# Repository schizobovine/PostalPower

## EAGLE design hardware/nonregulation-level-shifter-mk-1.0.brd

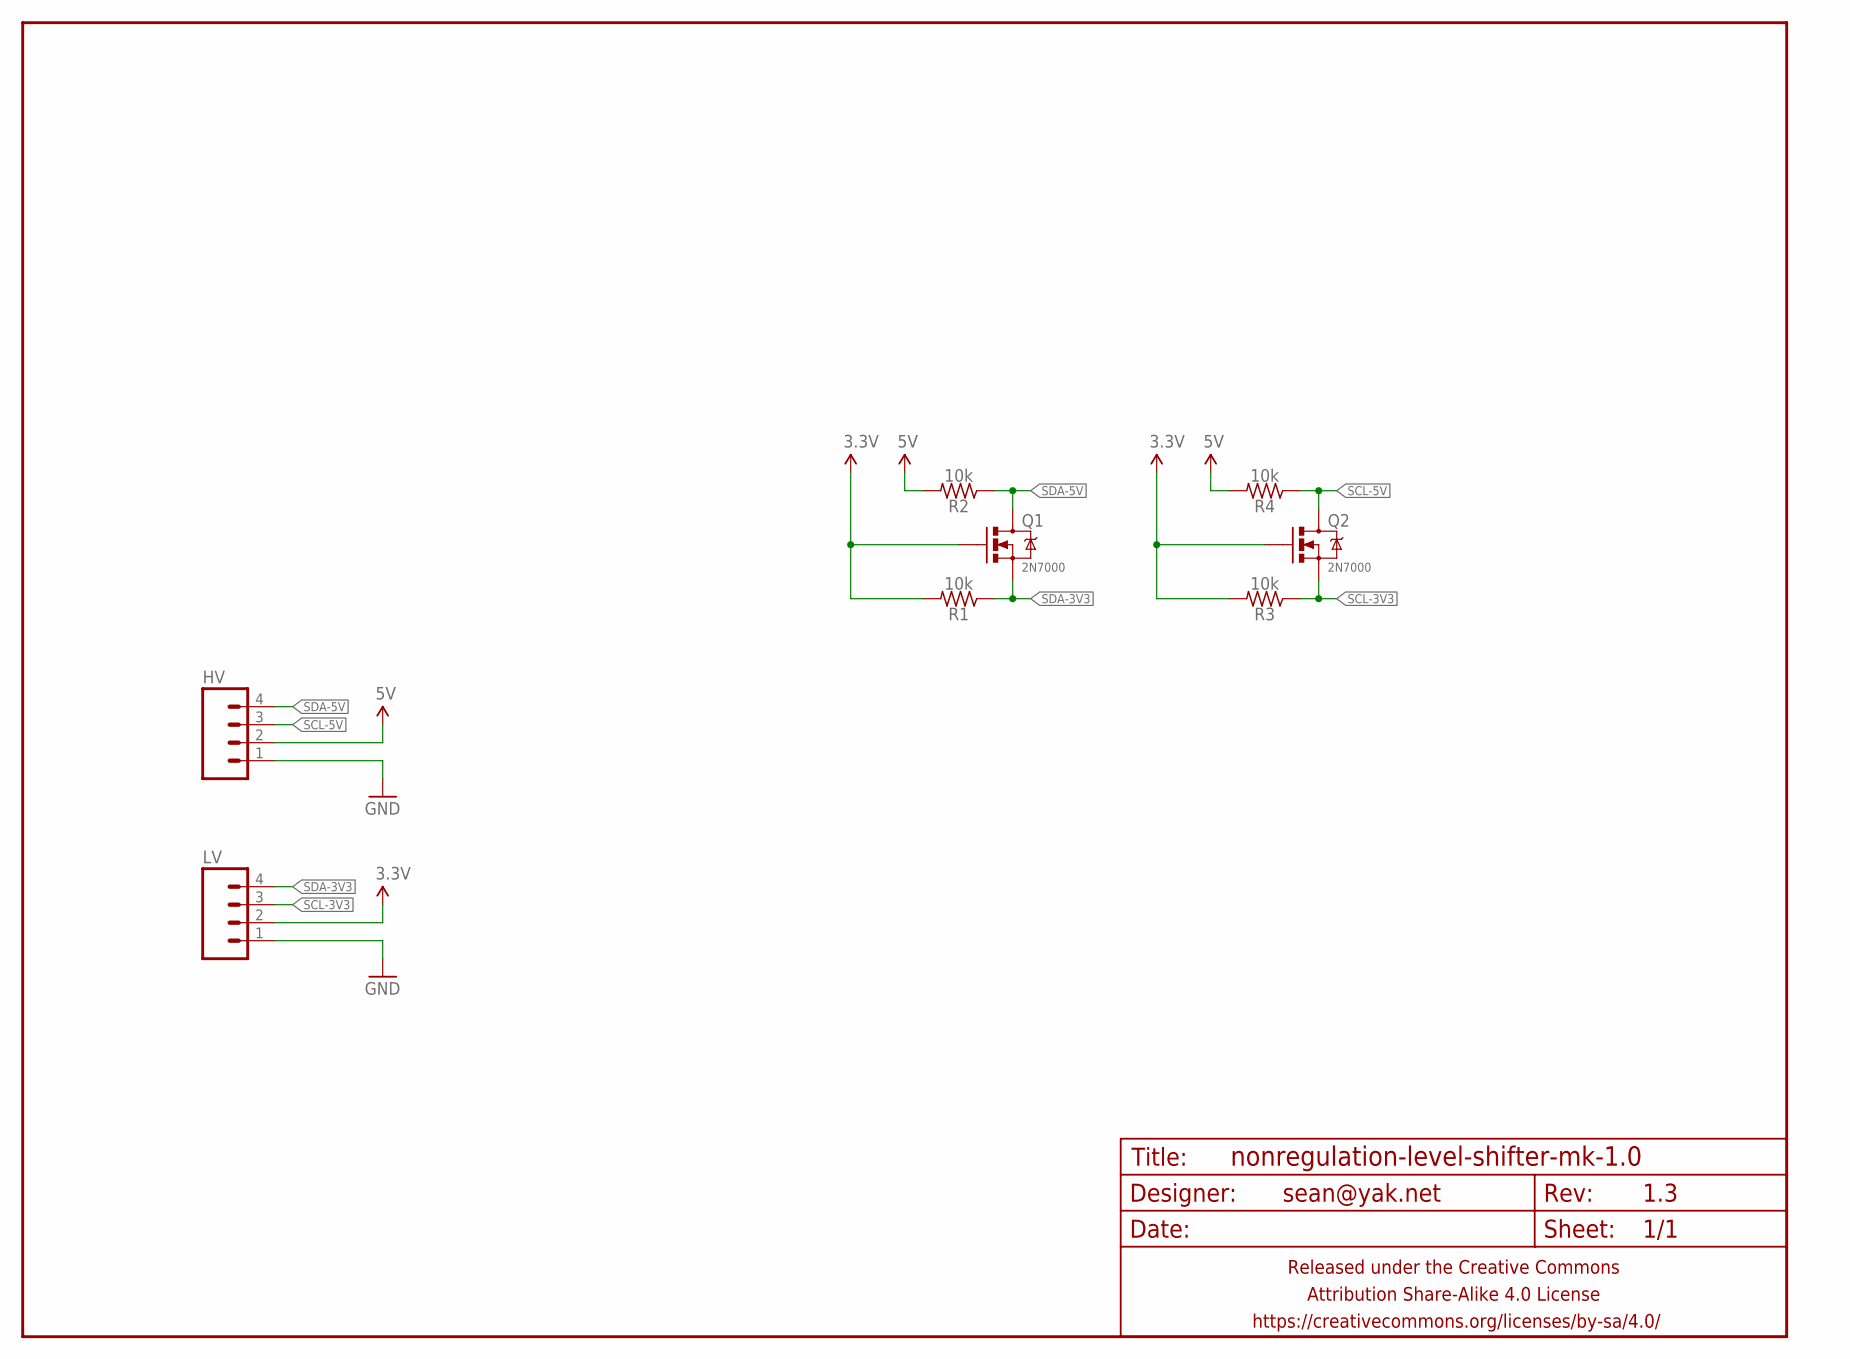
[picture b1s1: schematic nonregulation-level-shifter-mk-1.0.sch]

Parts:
FRAME1: FRAME-LETTERNO_PACKAGE; DUMMY
HV: M04PTH; 1X04-PTH-VERT
LV: M04PTH; 1X04-PTH-VERT
Q1, Q2: 2N7000; TO-92-AMMO
R1, R2, R3, R4: 10k; RESISTOR-AXIAL-PTH-5.08MM

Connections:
3.3V: LV.2, Q1.2 (G), Q2.2 (G), R1.P$2 (2), R3.P$2 (2)
5V: HV.2, R2.P$2 (2), R4.P$2 (2)
GND: HV.1, LV.1
SCL-3V3: LV.3, Q2.1 (S), R3.P$1 (1)
SCL-5V: HV.3, Q2.3 (D), R4.P$1 (1)
SDA-3V3: LV.4, Q1.1 (S), R1.P$1 (1)
SDA-5V: HV.4, Q1.3 (D), R2.P$1 (1)

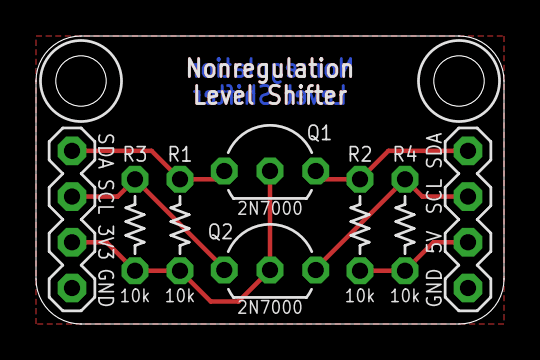
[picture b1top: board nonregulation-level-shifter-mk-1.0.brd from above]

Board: 2 copper layers, 26.0 x 16.0 mm, 10 parts (1 on the bottom side), 7 nets.

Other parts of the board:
U$1: CC-BY-SA-4.0-NO-URL

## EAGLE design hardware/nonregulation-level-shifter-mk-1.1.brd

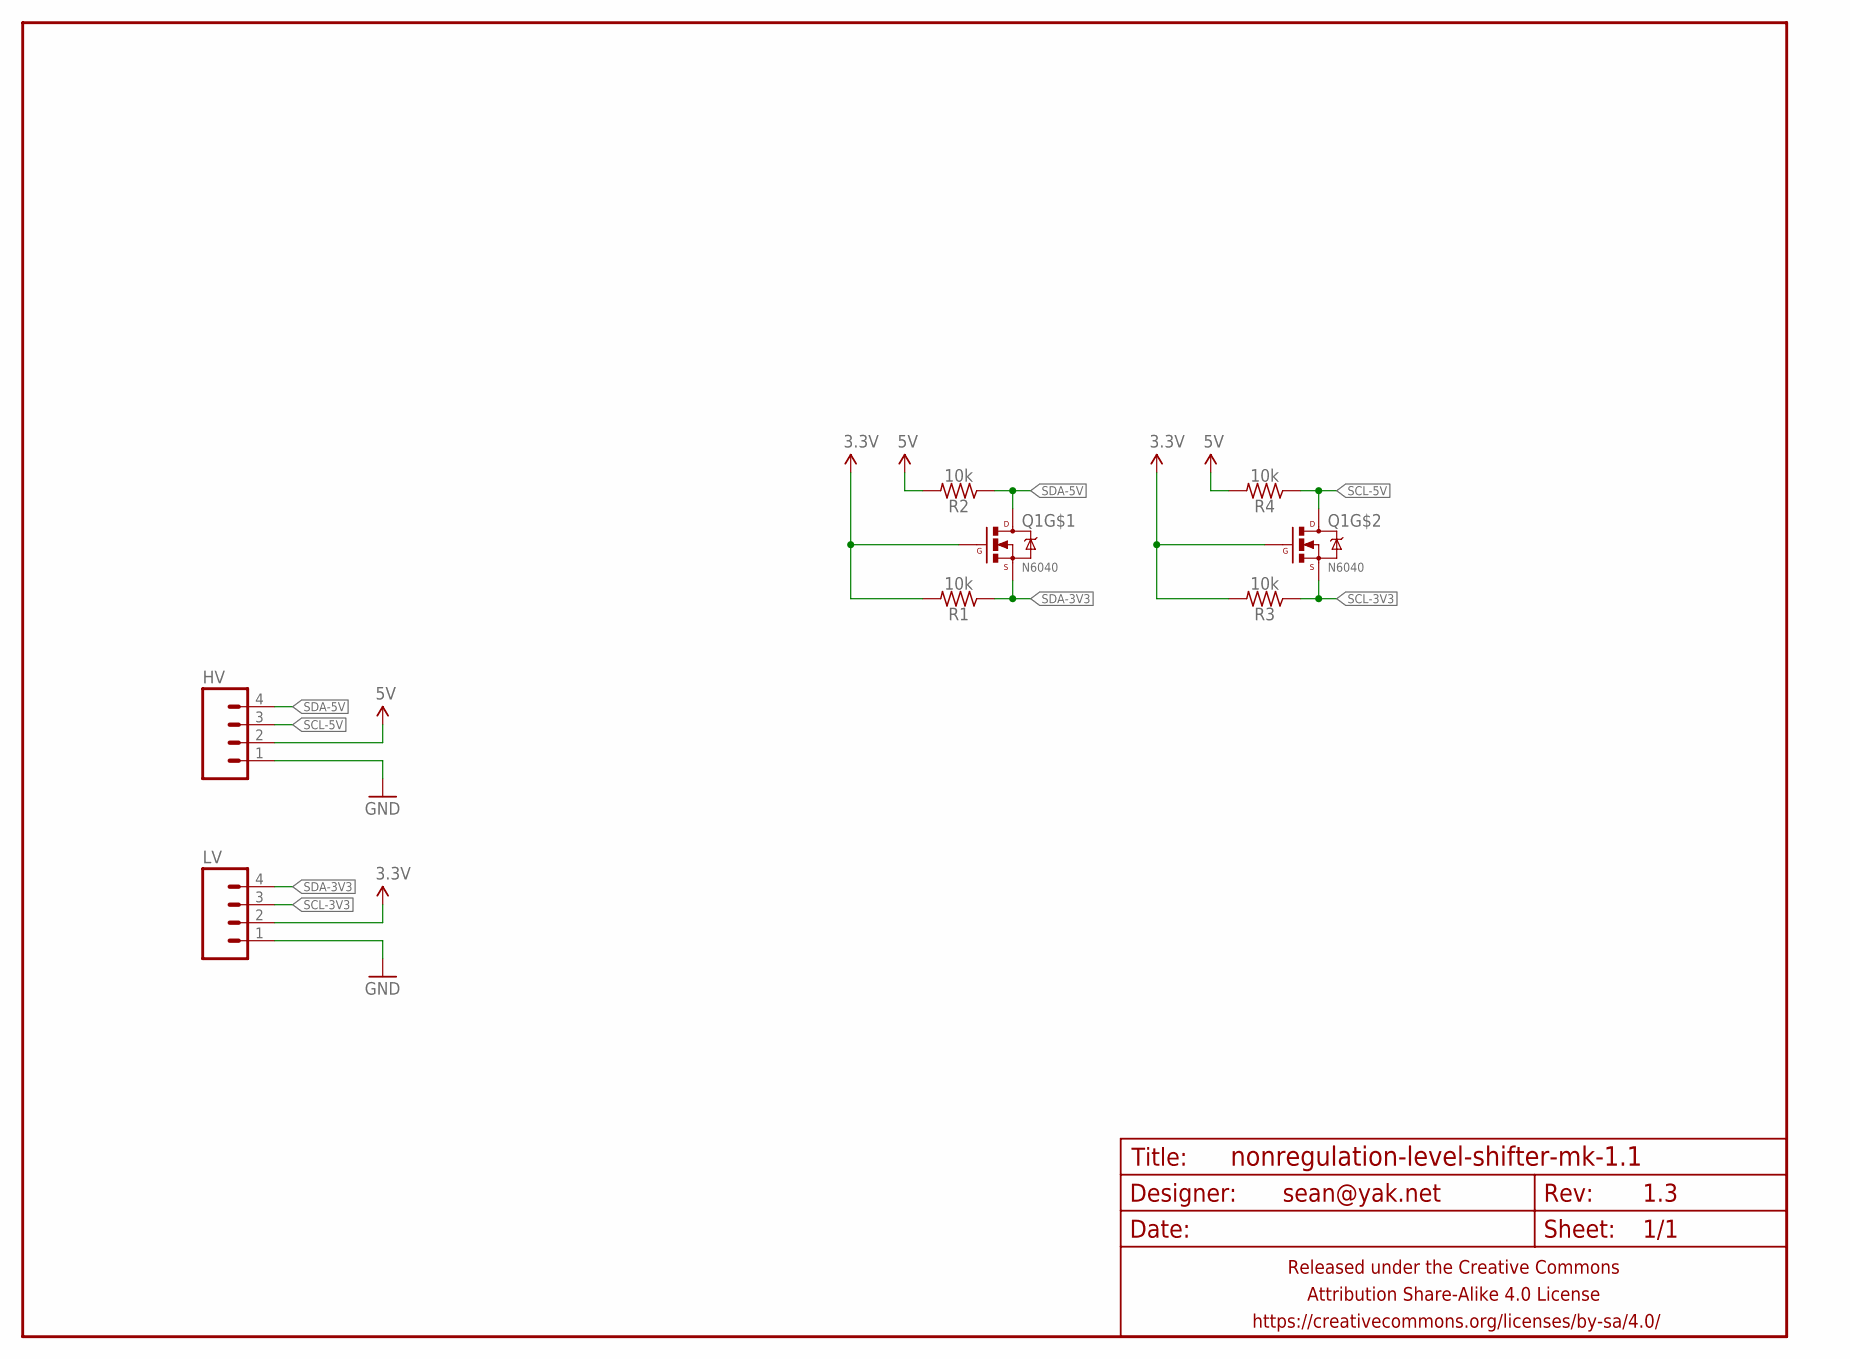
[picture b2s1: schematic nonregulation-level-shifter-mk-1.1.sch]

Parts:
FRAME1: FRAME-LETTERNO_PACKAGE; DUMMY
HV: M04PTH; 1X04-PTH-VERT
LV: M04PTH; 1X04-PTH-VERT
Q1: N6040; SO08
R1, R2, R3, R4: 10k; R0805

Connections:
3.3V: LV.2, Q1.2 (G), Q1.4 (G), R1.2, R3.2
5V: HV.2, R2.2, R4.2
GND: HV.1, LV.1
SCL-3V3: LV.3, Q1.3 (S), R3.1
SCL-5V: HV.3, Q1.5 (D), Q1.6 (D), R4.1
SDA-3V3: LV.4, Q1.1 (S), R1.1
SDA-5V: HV.4, Q1.7 (D), Q1.8 (D), R2.1

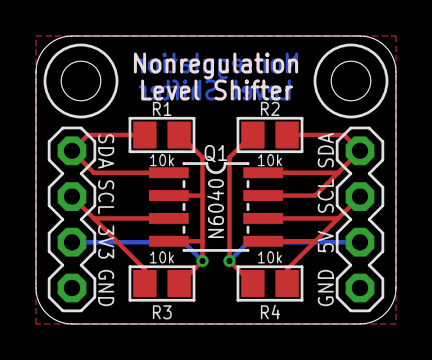
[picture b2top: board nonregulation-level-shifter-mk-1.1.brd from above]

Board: 2 copper layers, 20.0 x 16.0 mm, 9 parts (1 on the bottom side), 7 nets.

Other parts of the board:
U$1: CC-BY-SA-4.0-NO-URL

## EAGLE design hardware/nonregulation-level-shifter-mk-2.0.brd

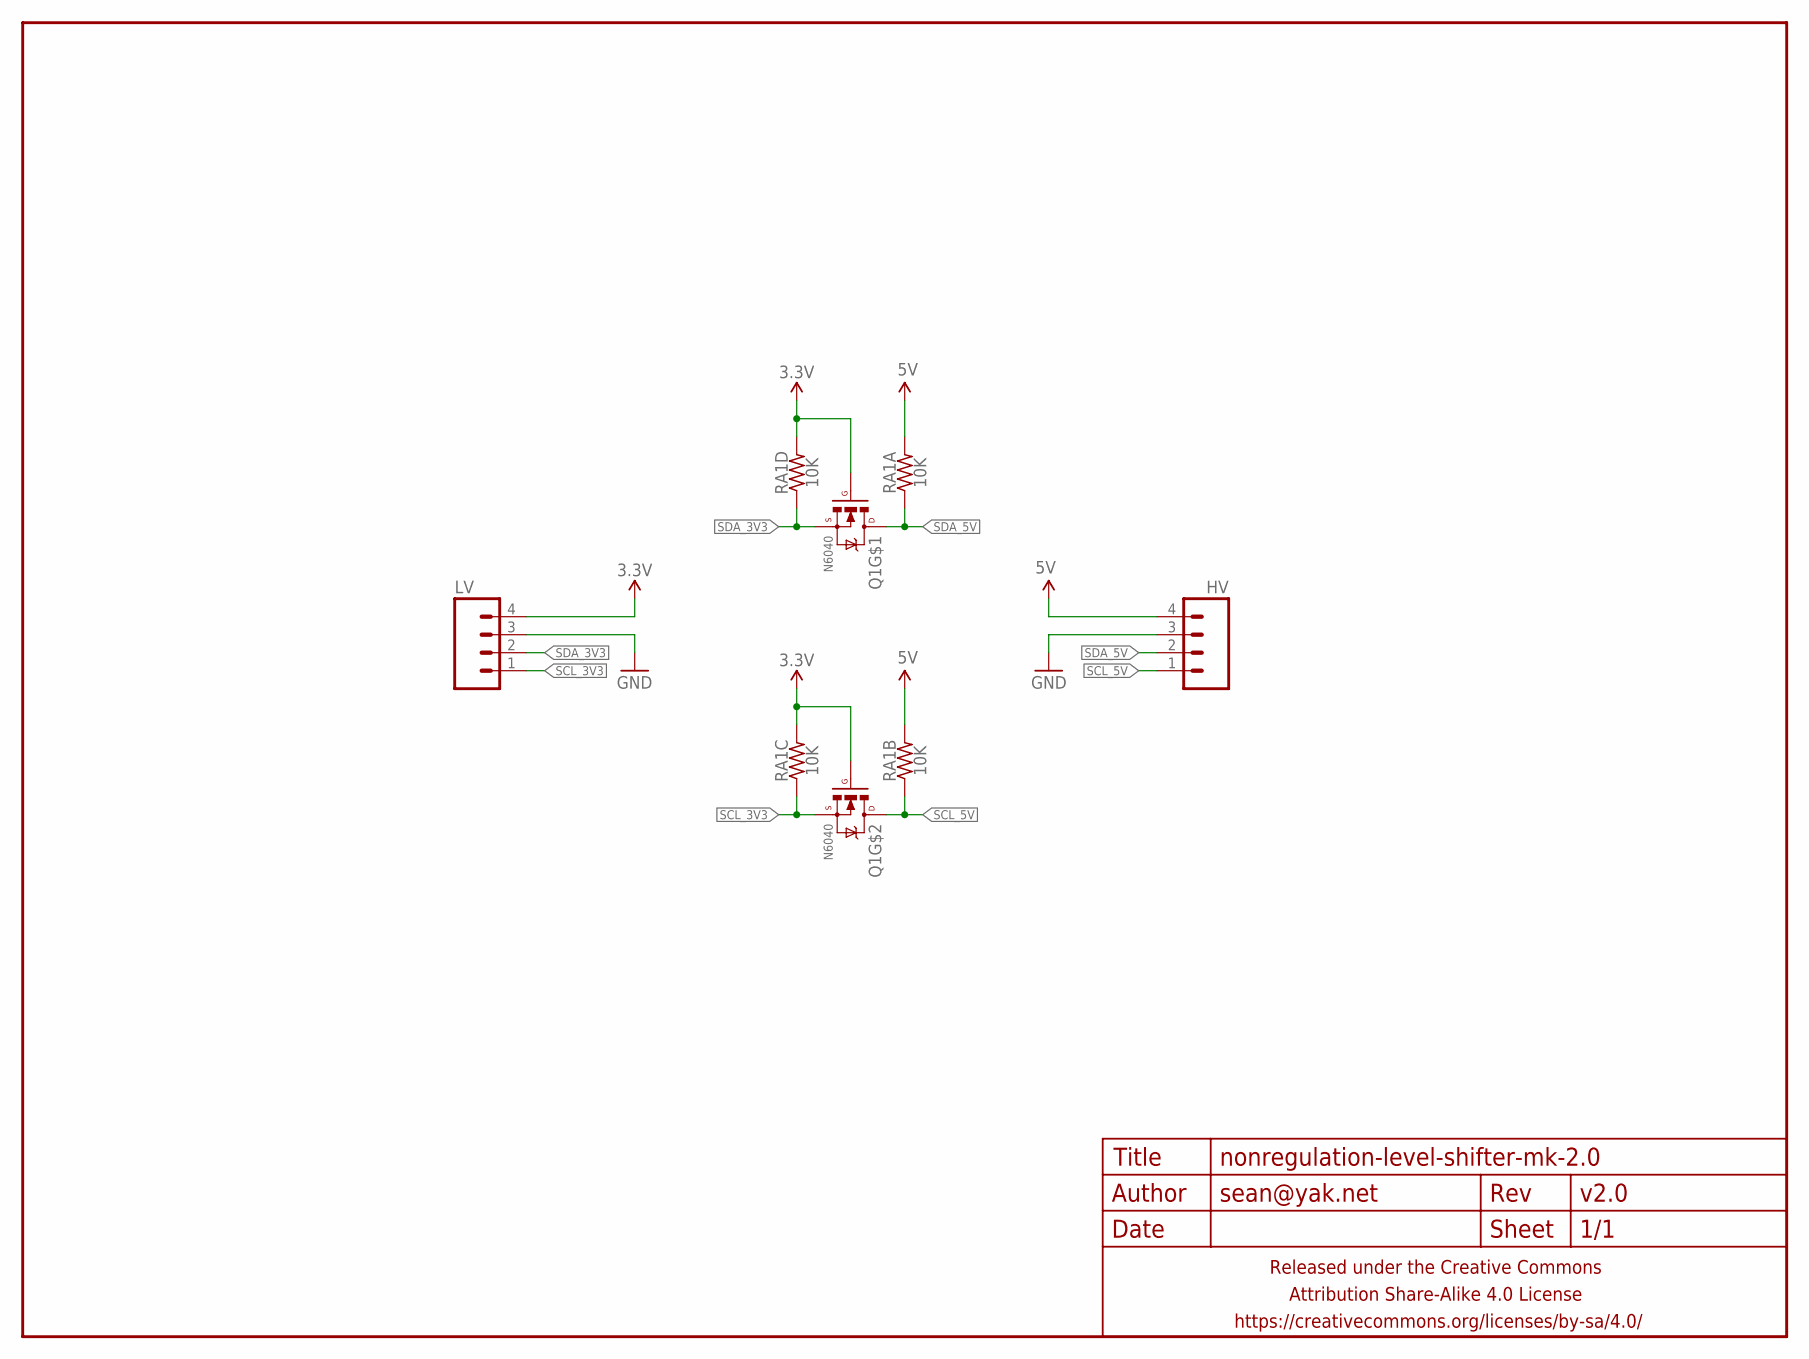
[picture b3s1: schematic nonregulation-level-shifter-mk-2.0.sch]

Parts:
FRAME1: FRAME-LETTERNO_PACKAGE; DUMMY
HV: M04PTH-CENTERED; 1X04-PTH-VERT-CENTER
LV: M04PTH-CENTERED; 1X04-PTH-VERT-CENTER
Q1: N6040; SO08
RA1: 10K; R1206-ARRAY-4

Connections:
3.3V: LV.4, Q1.2 (G), Q1.4 (G), RA1.C2 (2), RA1.D2 (2)
5V: HV.4, RA1.A2 (2), RA1.B2 (2)
GND: HV.3, LV.3
SCL_3V3: LV.1, Q1.3 (S), RA1.C1 (1)
SCL_5V: HV.1, Q1.5 (D), Q1.6 (D), RA1.B1 (1)
SDA_3V3: LV.2, Q1.1 (S), RA1.D1 (1)
SDA_5V: HV.2, Q1.7 (D), Q1.8 (D), RA1.A1 (1)

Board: 2 copper layers, 5 parts (0 on the bottom side), 7 nets, no tracks yet.

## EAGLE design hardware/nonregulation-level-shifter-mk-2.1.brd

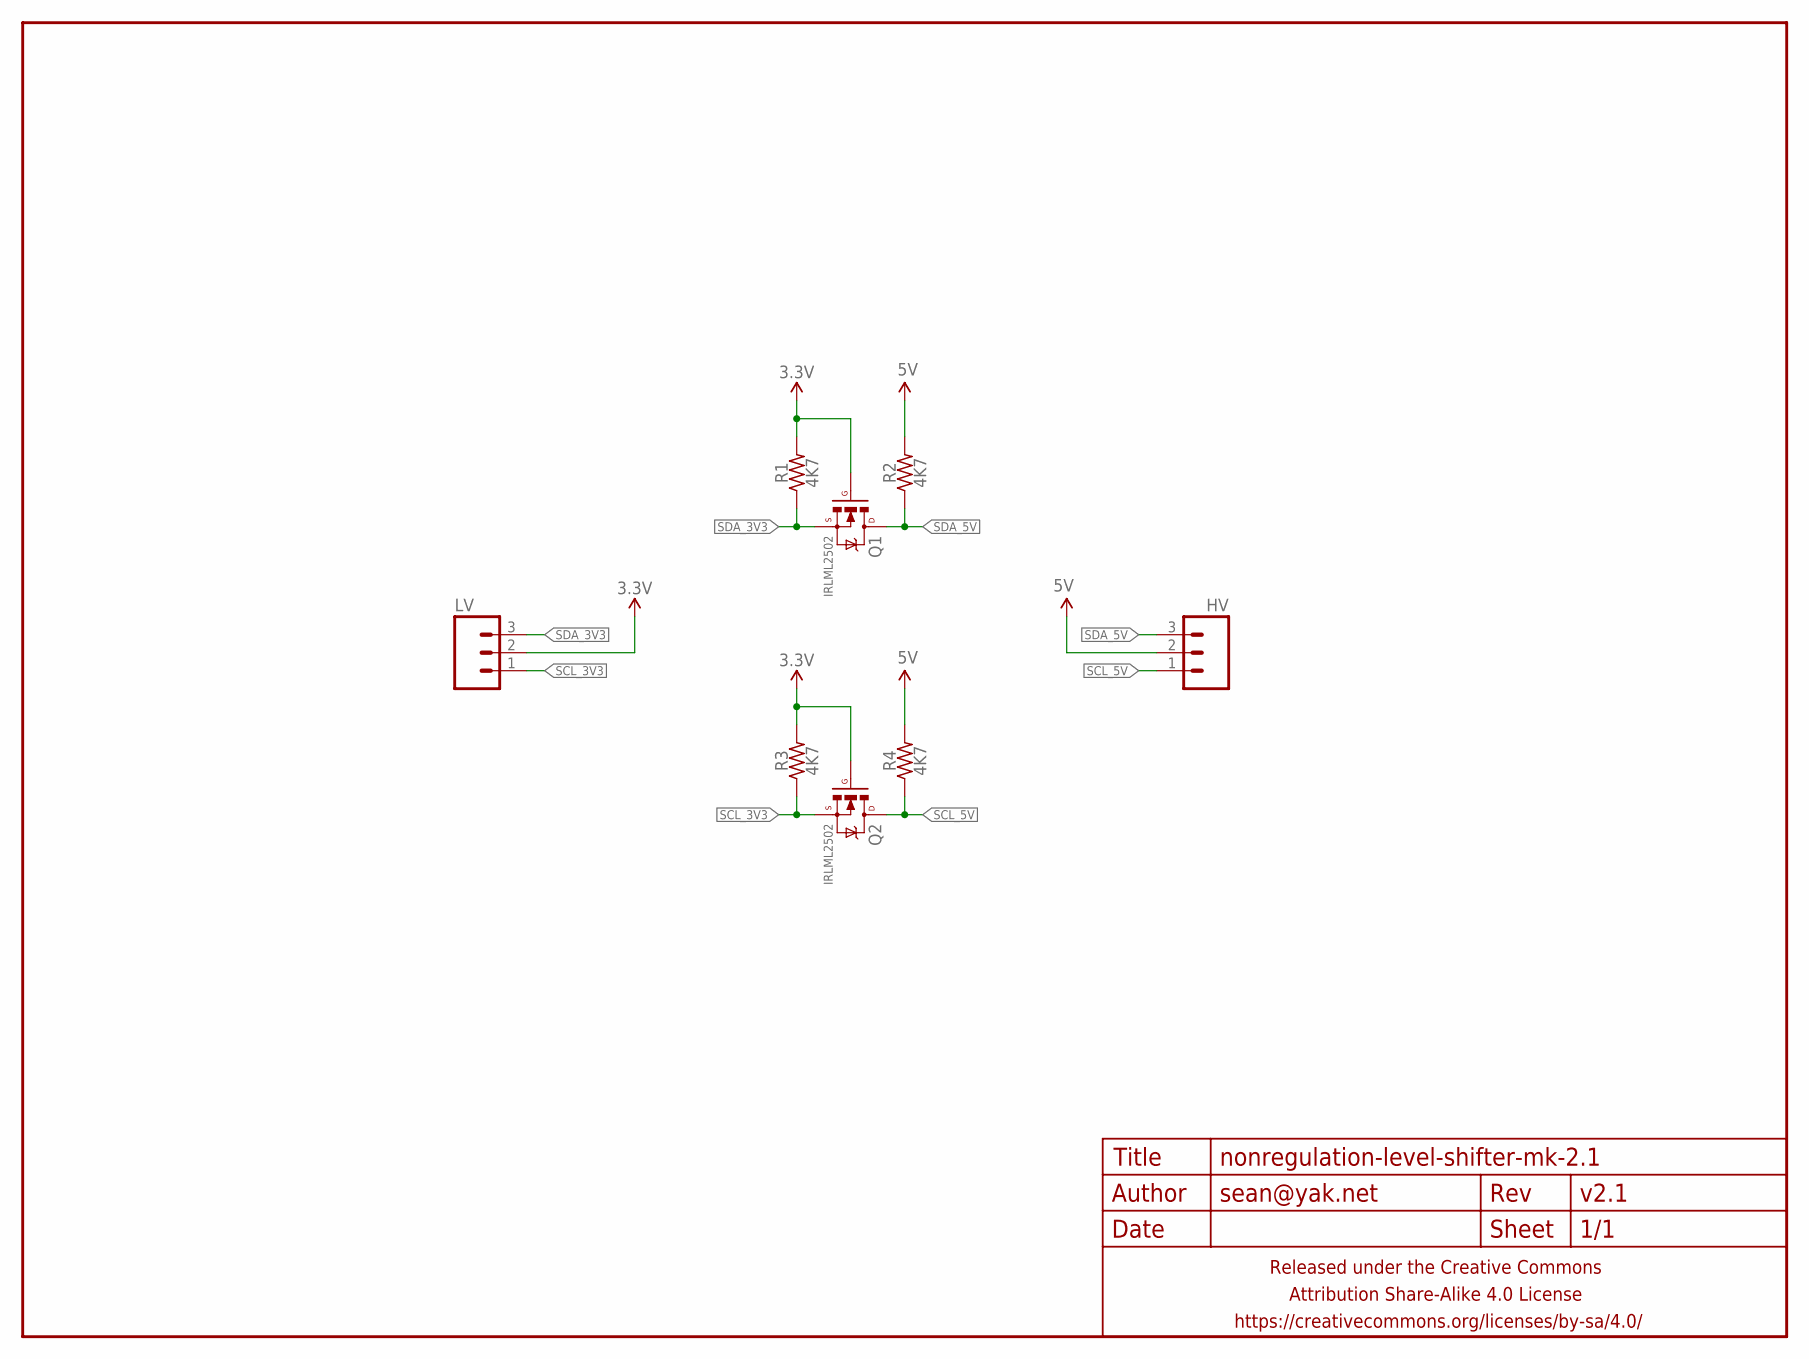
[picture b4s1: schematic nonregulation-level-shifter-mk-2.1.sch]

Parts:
FRAME1: FRAME-LETTERNO_PACKAGE; DUMMY
HV: M03PTH-CENTERED; 1X03-CENTERED
LV: M03PTH-CENTERED; 1X03-CENTERED
Q1, Q2: IRLML2502; SOT23
R1, R2, R3, R4: 4K7; R0603

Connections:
3.3V: LV.2, Q1.1 (G), Q2.1 (G), R1.2, R3.2
5V: HV.2, R2.2, R4.2
SCL_3V3: LV.1, Q2.2 (S), R3.1
SCL_5V: HV.1, Q2.3 (D), R4.1
SDA_3V3: LV.3, Q1.2 (S), R1.1
SDA_5V: HV.3, Q1.3 (D), R2.1

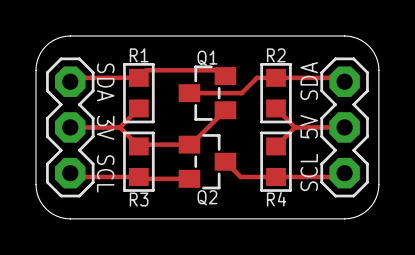
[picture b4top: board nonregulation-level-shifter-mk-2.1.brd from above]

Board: 2 copper layers, 19.1 x 10.2 mm, 10 parts (1 on the bottom side), 6 nets.

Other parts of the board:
U$1: COW_SMALL_NOTEXT

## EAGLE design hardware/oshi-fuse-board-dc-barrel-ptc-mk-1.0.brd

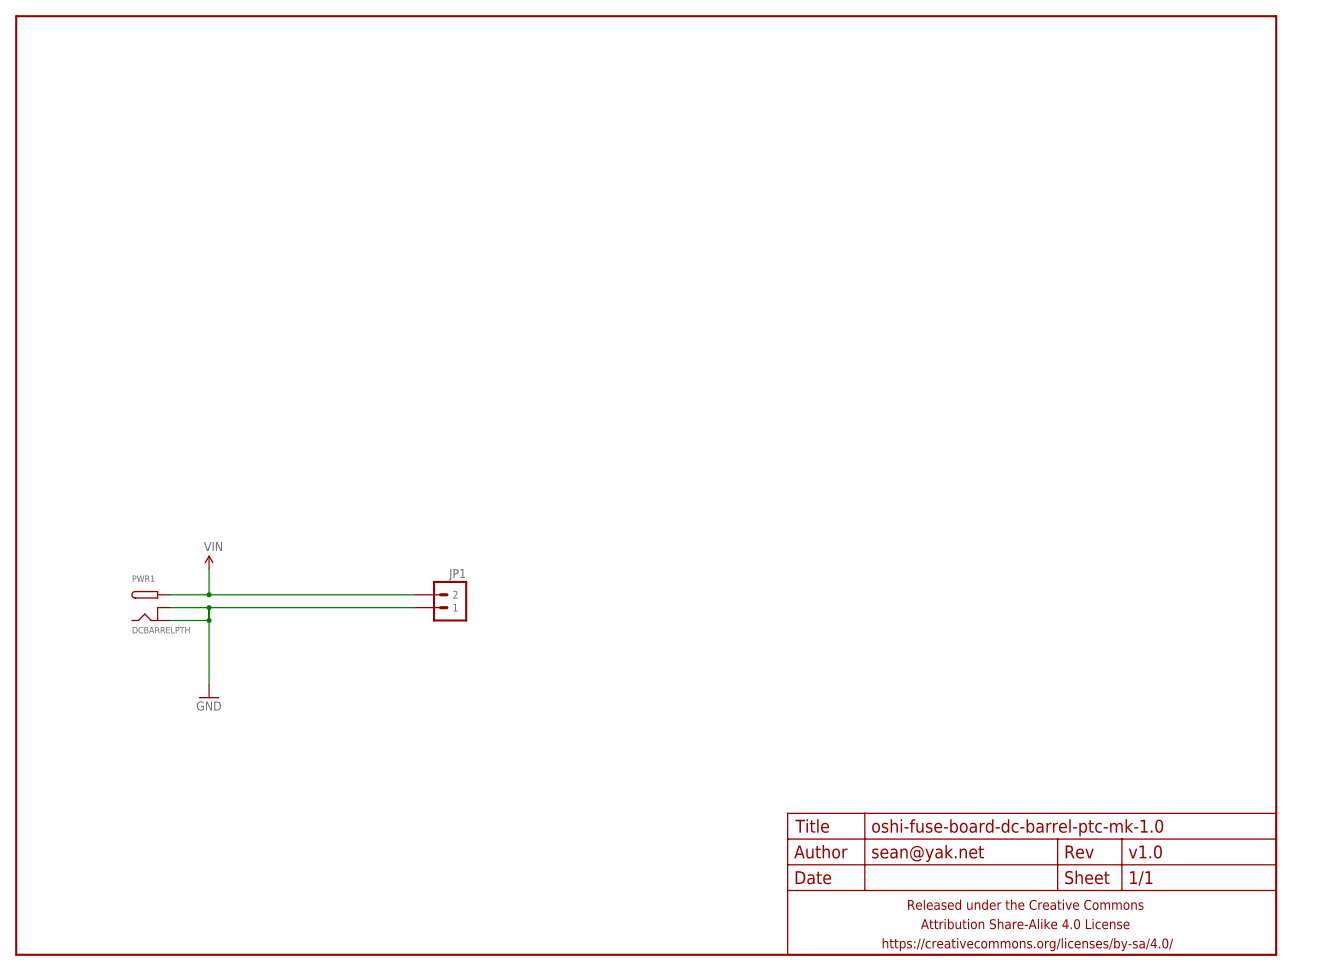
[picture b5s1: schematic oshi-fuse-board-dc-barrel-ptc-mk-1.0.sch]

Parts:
FRAME1: FRAME-LETTERNO_PACKAGE; DUMMY
JP1: M02PTH-CENTERED-R+; 1X02-CENTER-R+
PWR1: DCBARRELPTH; DCJACK_2MM_PTH

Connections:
GND: JP1.1, PWR1.BRK, PWR1.GND
VIN: JP1.2, PWR1.PWR

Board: 2 copper layers, 3 parts (0 on the bottom side), 2 nets, no tracks yet.

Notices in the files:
parts and their libraries:
A_butts: Released under the Creative Commons Attribution Share-Alike 4.0 License
A_butts: https://creativecommons.org/licenses/by-sa/4.0
A_butts: Released under the Creative Commons
